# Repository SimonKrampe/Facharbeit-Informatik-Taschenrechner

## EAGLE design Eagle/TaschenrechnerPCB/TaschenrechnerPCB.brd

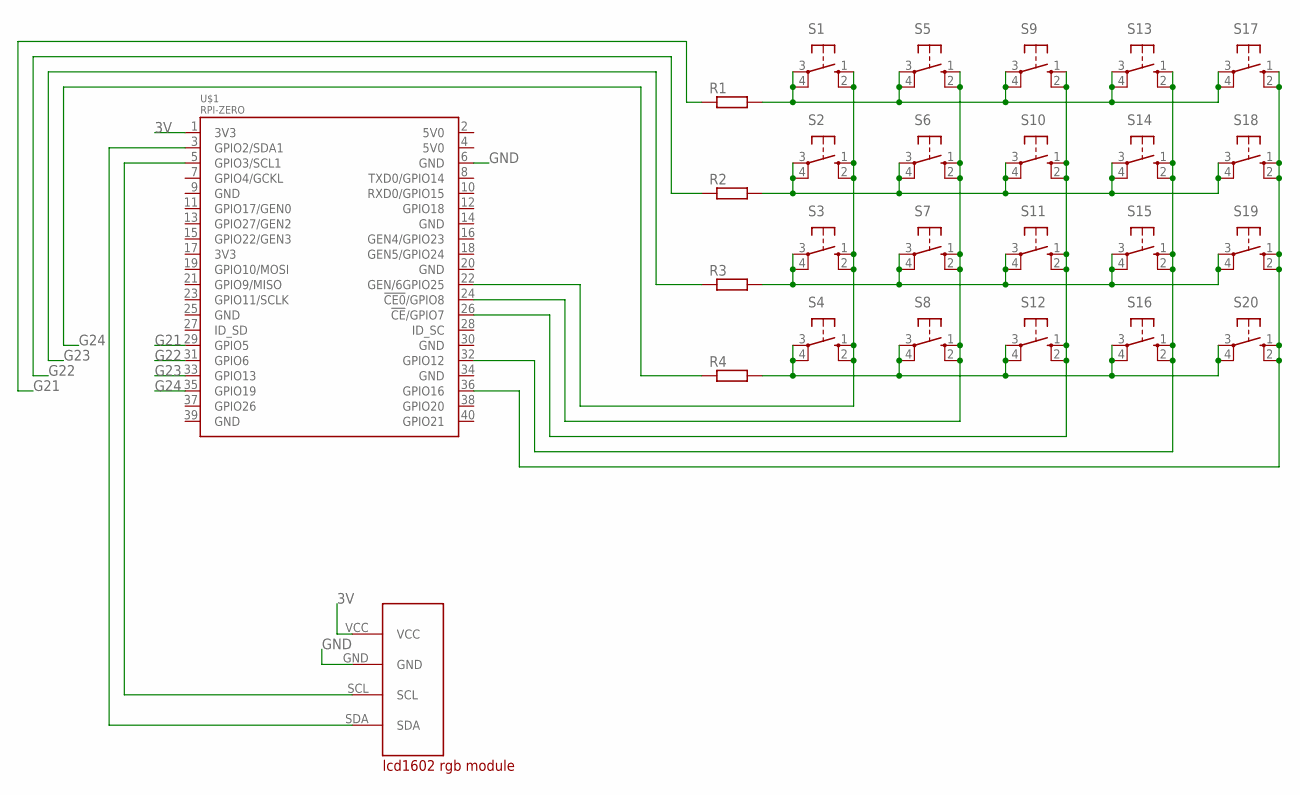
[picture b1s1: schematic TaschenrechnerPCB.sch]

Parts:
R1, R2, R3, R4: R-EU_0207/10; 0207/10
S1, S2, S3, S4, S5, S6, S7, S8, S9, S10, S11, S12, S13, S14, S15, S16, S17, S18, S19, S20: 10-XX; B3F-10XX
U$1: RPI-ZERO; RASP_PI_ZERO_BOARD_FULL
U$2: LCD1602-RGB-MODULE

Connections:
3V: U$1.1 (3V3), U$2.VCC
G6: S1.1 (S), S1.2 (S1), S2.1 (S), S2.2 (S1), S3.1 (S), S3.2 (S1), S4.1 (S), S4.2 (S1), U$1.22 (GEN/6GPIO25)
G10: S5.1 (S), S5.2 (S1), S6.1 (S), S6.2 (S1), S7.1 (S), S7.2 (S1), S8.1 (S), S8.2 (S1), U$1.24 (!CE0!/GPIO8)
G11: S9.1 (S), S9.2 (S1), S10.1 (S), S10.2 (S1), S11.1 (S), S11.2 (S1), S12.1 (S), S12.2 (S1), U$1.26 (!CE!/GPIO7)
G21: R1.1, U$1.29 (GPIO5)
G22: R2.1, U$1.31 (GPIO6)
G23: R3.1, U$1.33 (GPIO13)
G24: R4.1, U$1.35 (GPIO19)
G26: S13.1 (S), S13.2 (S1), S14.1 (S), S14.2 (S1), S15.1 (S), S15.2 (S1), S16.1 (S), S16.2 (S1), U$1.32 (GPIO12)
G27: S17.1 (S), S17.2 (S1), S18.1 (S), S18.2 (S1), S19.1 (S), S19.2 (S1), S20.1 (S), S20.2 (S1), U$1.36 (GPIO16)
GND: U$1.6 (GND), U$2.GND
unnamed: U$1.3 (GPIO2/SDA1), U$2.SDA
unnamed: U$1.5 (GPIO3/SCL1), U$2.SCL
unnamed: R1.2, S1.3, S1.4 (P1), S5.3, S5.4 (P1), S9.3, S9.4 (P1), S13.3, S13.4 (P1), S17.3, S17.4 (P1)
unnamed: R2.2, S2.3, S2.4 (P1), S6.3, S6.4 (P1), S10.3, S10.4 (P1), S14.3, S14.4 (P1), S18.3, S18.4 (P1)
unnamed: R3.2, S3.3, S3.4 (P1), S7.3, S7.4 (P1), S11.3, S11.4 (P1), S15.3, S15.4 (P1), S19.3, S19.4 (P1)
unnamed: R4.2, S4.3, S4.4 (P1), S8.3, S8.4 (P1), S12.3, S12.4 (P1), S16.3, S16.4 (P1), S20.3, S20.4 (P1)

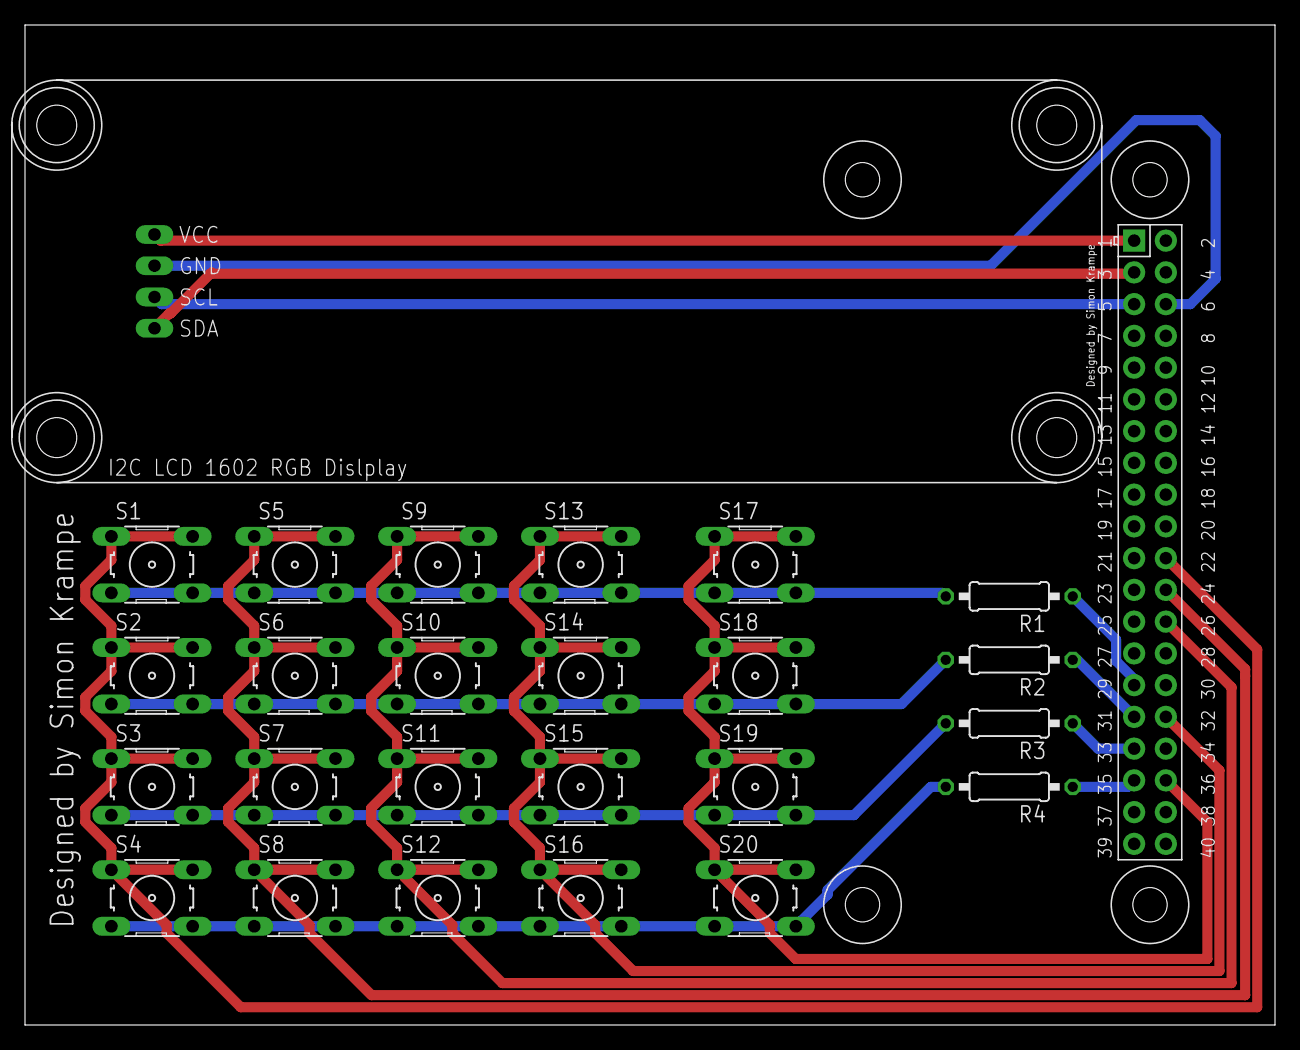
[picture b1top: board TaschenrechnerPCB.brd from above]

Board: 2 copper layers, 100.0 x 80.0 mm, 26 parts (0 on the bottom side), 17 nets.

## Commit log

2022-02-15 Wichtige Dateien
    Hinzufügen wichtiger Dateien zur Repo
2022-02-15 Eagle, Fritzing und Bilder hinzugefügt
2022-02-15 Literaturverzeichnis fertig
2022-02-16 Finale änderungen
2022-02-17 Einige Dateien hinzugefügt
2022-02-18 Formatierungsänderungen + einige Dateien
